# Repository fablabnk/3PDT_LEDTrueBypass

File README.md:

3PDT true bypass following https://stinkfoot.se/archives/2233

3PDT switch is inserted into the top side of the PCB
Point-to-point wiring from pin headers is done from the bottom side

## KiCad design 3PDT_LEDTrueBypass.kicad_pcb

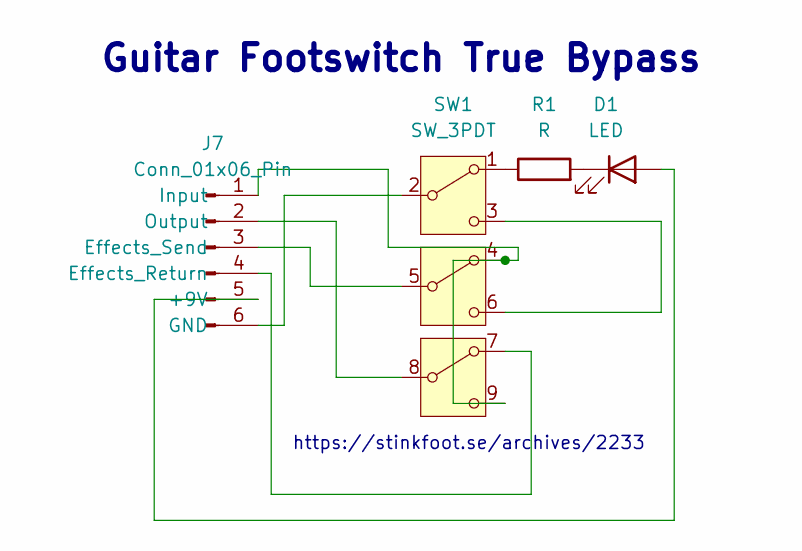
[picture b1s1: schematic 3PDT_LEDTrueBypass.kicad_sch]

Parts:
D1: LED; PinHeader_1x02_P2.54mm_Vertical
J7: Conn_01x06_Pin; PinHeader_1x06_P2.54mm_Vertical
R1: R; R_Axial_DIN0207_L6.3mm_D2.5mm_P7.62mm_Horizontal
SW1: SW_3PDT; STOMP-SWITCH-3PDT_DaierTek

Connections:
unnamed: D1.2 (A), J7.5 (+9V)
unnamed: D1.1 (K), R1.2
unnamed: J7.4 (Effects_Return), SW1.7 (G)
unnamed: J7.3 (Effects_Send), SW1.5 (E)
unnamed: J7.6 (GND), SW1.2 (B)
unnamed: J7.1 (Input), SW1.4 (D), SW1.9 (I)
unnamed: J7.2 (Output), SW1.8 (H)
unnamed: R1.1, SW1.1 (A)
unnamed: SW1.3 (C), SW1.6 (F)

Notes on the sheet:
Guitar Footswitch True Bypass
https://stinkfoot.se/archives/2233

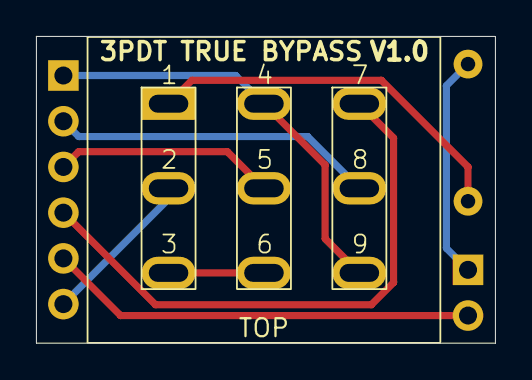
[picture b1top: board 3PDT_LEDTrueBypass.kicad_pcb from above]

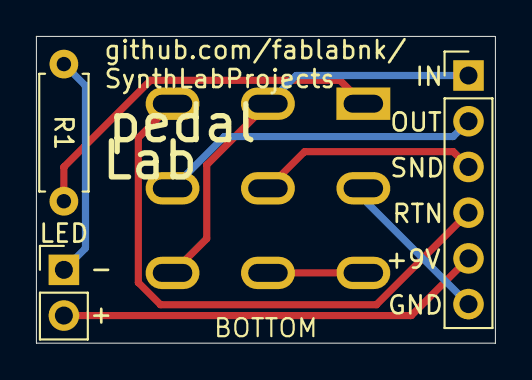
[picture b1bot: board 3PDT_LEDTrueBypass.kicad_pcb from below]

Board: 2 copper layers, 25.5 x 17.0 mm, 4 parts (3 on the bottom side), 9 nets.

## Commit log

2024-07-26 overhauled, rerouted and fixed pin spacings - vertical and horizontal spacings were mixed up
